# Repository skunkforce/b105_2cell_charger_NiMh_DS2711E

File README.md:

# edgy_board number b105
This design is part of the [edgy board project](https://github.com/skunkforce/edgy_boards). 

# getting started
This repository uses submodules. After cloning use the command 

```$ git submodule update --init --recursive```

to pull the submodules before opening the project with kicad. 

# Tests
Tests can be found in [TESTS.md](TESTS.md)

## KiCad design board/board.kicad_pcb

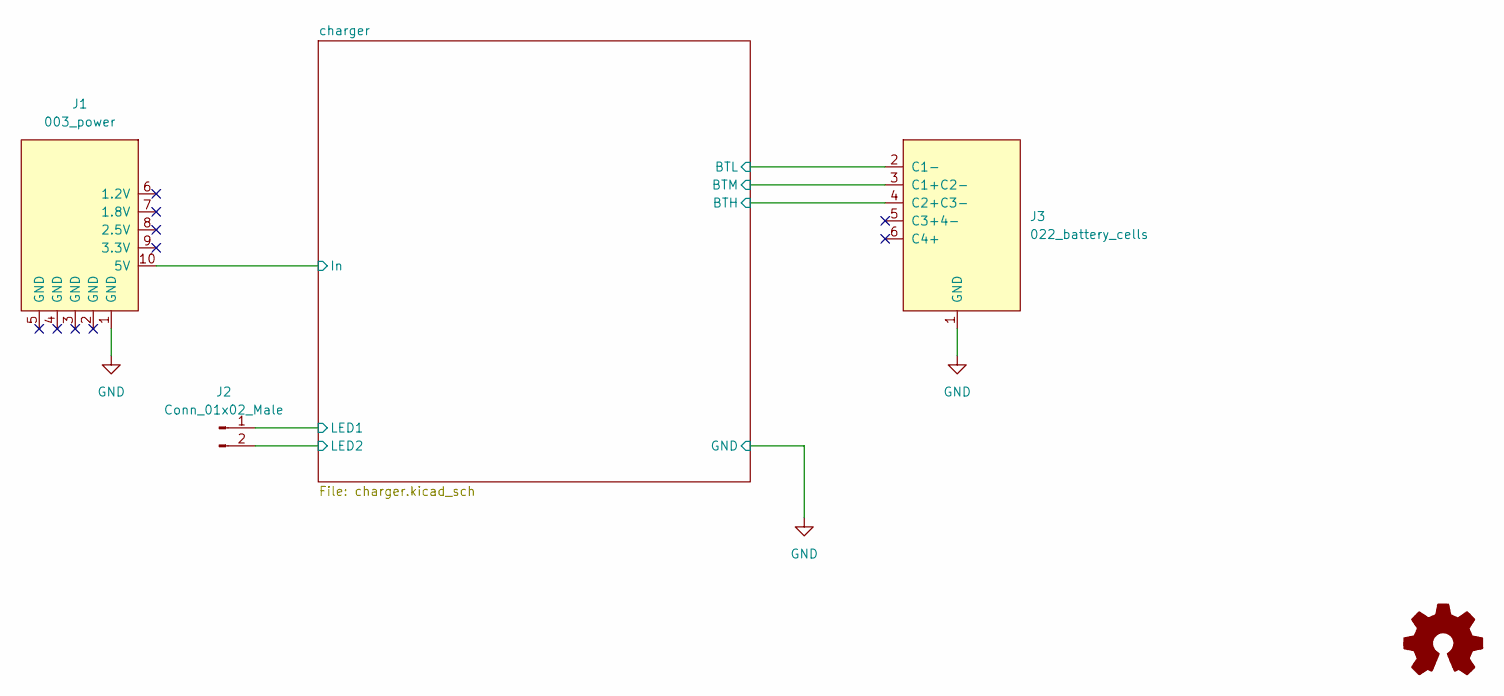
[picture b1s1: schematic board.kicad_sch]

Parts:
J1: 003_power; on_edge_2x05_device
J2: Conn_01x02_Male; PinHeader_1x02_P2.54mm_Vertical
J3: 022_battery_cells; on_edge_2x05_host
LOGO1: Logo_Open_Hardware_Small; OSHW-Symbol_6.7x6mm_SilkScreen

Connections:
/charger/BTH: J3.4 (C2+C3-); also elsewhere on the board
/charger/BTL: J3.2 (C1-); also elsewhere on the board
/charger/BTM: J3.3 (C1+C2-); also elsewhere on the board
/charger/In: J1.10 (5V); also elsewhere on the board
/charger/LED1: J2.1; also elsewhere on the board
/charger/LED2: J2.2; also elsewhere on the board
GND: J1.1 (GND), J3.1 (GND); also elsewhere on the board

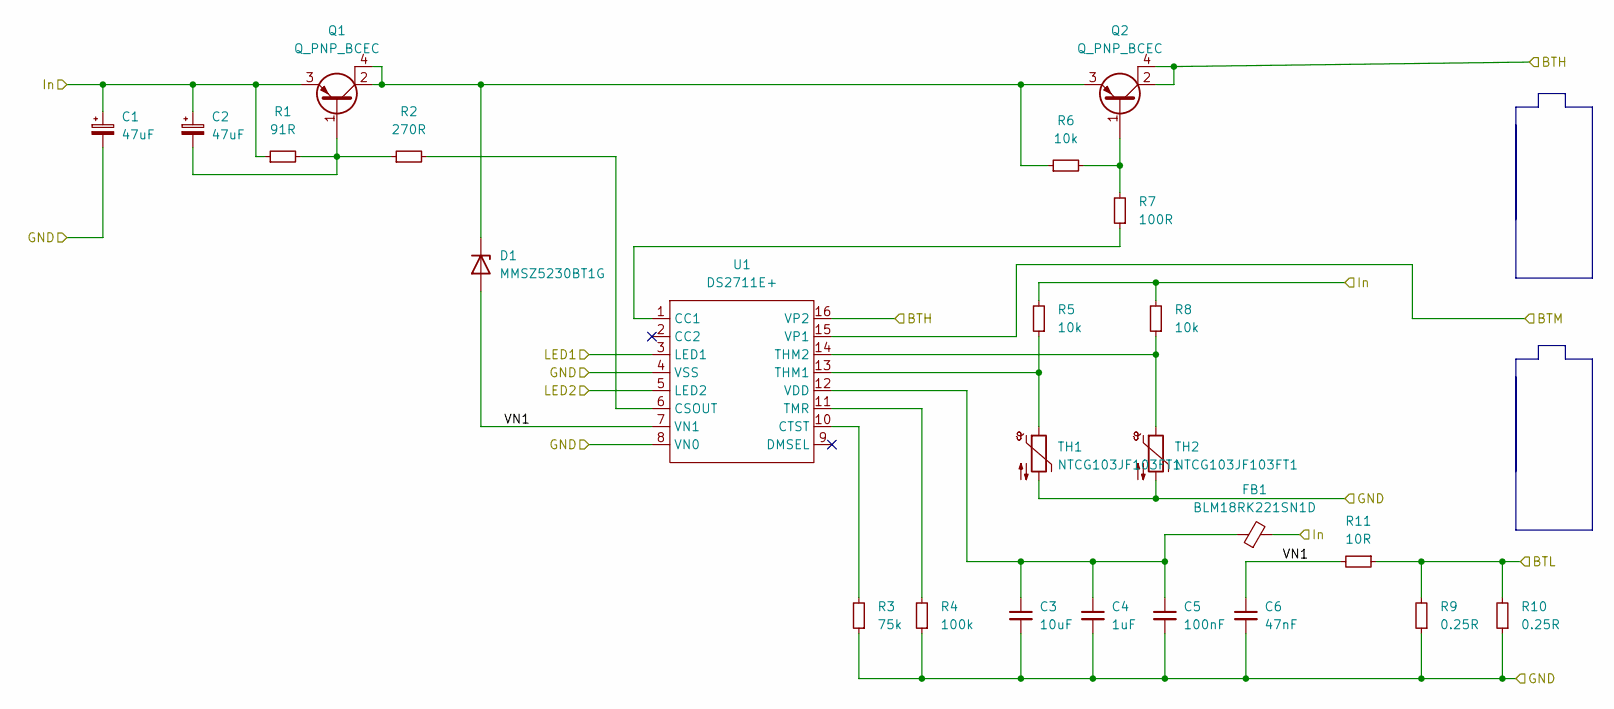
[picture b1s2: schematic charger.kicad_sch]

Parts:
C1, C2: 47uF; C_1210_3225Metric; MPN TAJB476K010RNJ
C3: 10uF; C_0603_1608Metric
C4: 1uF; C_0603_1608Metric
C5: 100nF; C_0603_1608Metric
C6: 47nF; C_0603_1608Metric
D1: MMSZ5230BT1G; D_SOD-123; MPN MMSZ5230BT1G
FB1: BLM18RK221SN1D; C_0603_1608Metric
Q1, Q2: Q_PNP_BCEC; TO-252-3_TabPin4; MPN MJD45H11T4G
R1: 91R; R_0603_1608Metric
R2: 270R; R_0603_1608Metric
R3: 75k; R_0603_1608Metric
R4: 100k; R_0603_1608Metric
R5, R6, R8: 10k; R_0603_1608Metric
R7: 100R; R_0603_1608Metric
R9, R10: 0.25R; R_1206_3216Metric
R11: 10R; R_0603_1608Metric
TH1, TH2: NTCG103JF103FT1; R_0402_1005Metric; MPN NTCG103JF103FT1
U1: DS2711E+; SOP65P640X110-16N; MPN DS2711E+

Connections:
/charger/BTH: Q2.2 (C), Q2.4 (C), U1.16 (VP2); also elsewhere on the board
/charger/BTL: R9.2, R10.2, R11.1; also elsewhere on the board
/charger/BTM: U1.15 (VP1); also elsewhere on the board
/charger/In: C1.1, C2.1, FB1.2, Q1.3 (E), R1.1, R5.2, R8.2; also elsewhere on the board
/charger/LED1: U1.3 (LED1); also elsewhere on the board
/charger/LED2: U1.5 (LED2); also elsewhere on the board
/charger/VN1: C6.1, D1.2 (A), R11.2, U1.7 (VN1)
GND: C1.2, C3.2, C4.2, C5.2, C6.2, R3.1, R4.1, R9.1, R10.1, TH1.2, TH2.2, U1.4 (VSS), U1.8 (VN0); also elsewhere on the board
unnamed: C2.2, Q1.1 (B), R1.2, R2.1
unnamed: C3.1, C4.1, C5.1, FB1.1, U1.12 (VDD)
unnamed: D1.1 (K), Q1.2 (C), Q1.4 (C), Q2.3 (E), R6.1
unnamed: Q2.1 (B), R6.2, R7.2
unnamed: R2.2, U1.6 (CSOUT)
unnamed: R3.2, U1.10 (CTST)
unnamed: R4.2, U1.11 (TMR)
unnamed: R5.1, TH1.1, U1.13 (THM1)
unnamed: R7.1, U1.1 (CC1)
unnamed: R8.1, TH2.1, U1.14 (THM2)

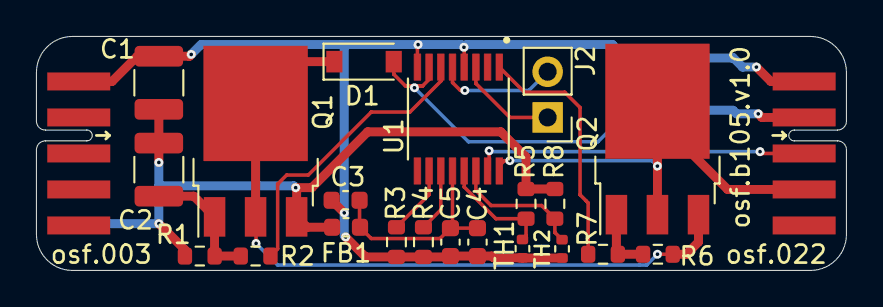
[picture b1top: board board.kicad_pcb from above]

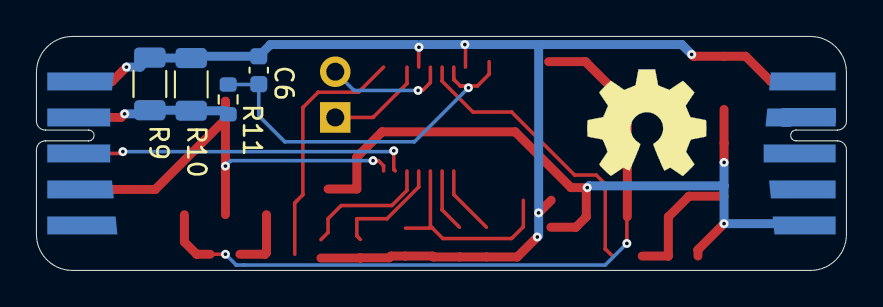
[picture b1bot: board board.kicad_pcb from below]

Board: 2 copper layers, 45.0 x 13.0 mm, 28 parts (5 on the bottom side), 18 nets.

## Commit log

2023-03-06 initial
2023-03-09 fixed missing connection
2023-04-13 fixed footprint
2023-05-25 added missing limmiting resistor to protect zener diode
